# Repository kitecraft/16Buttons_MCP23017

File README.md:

# 16Buttons_MCP23017
A 16 button board using a MCP23017 IC

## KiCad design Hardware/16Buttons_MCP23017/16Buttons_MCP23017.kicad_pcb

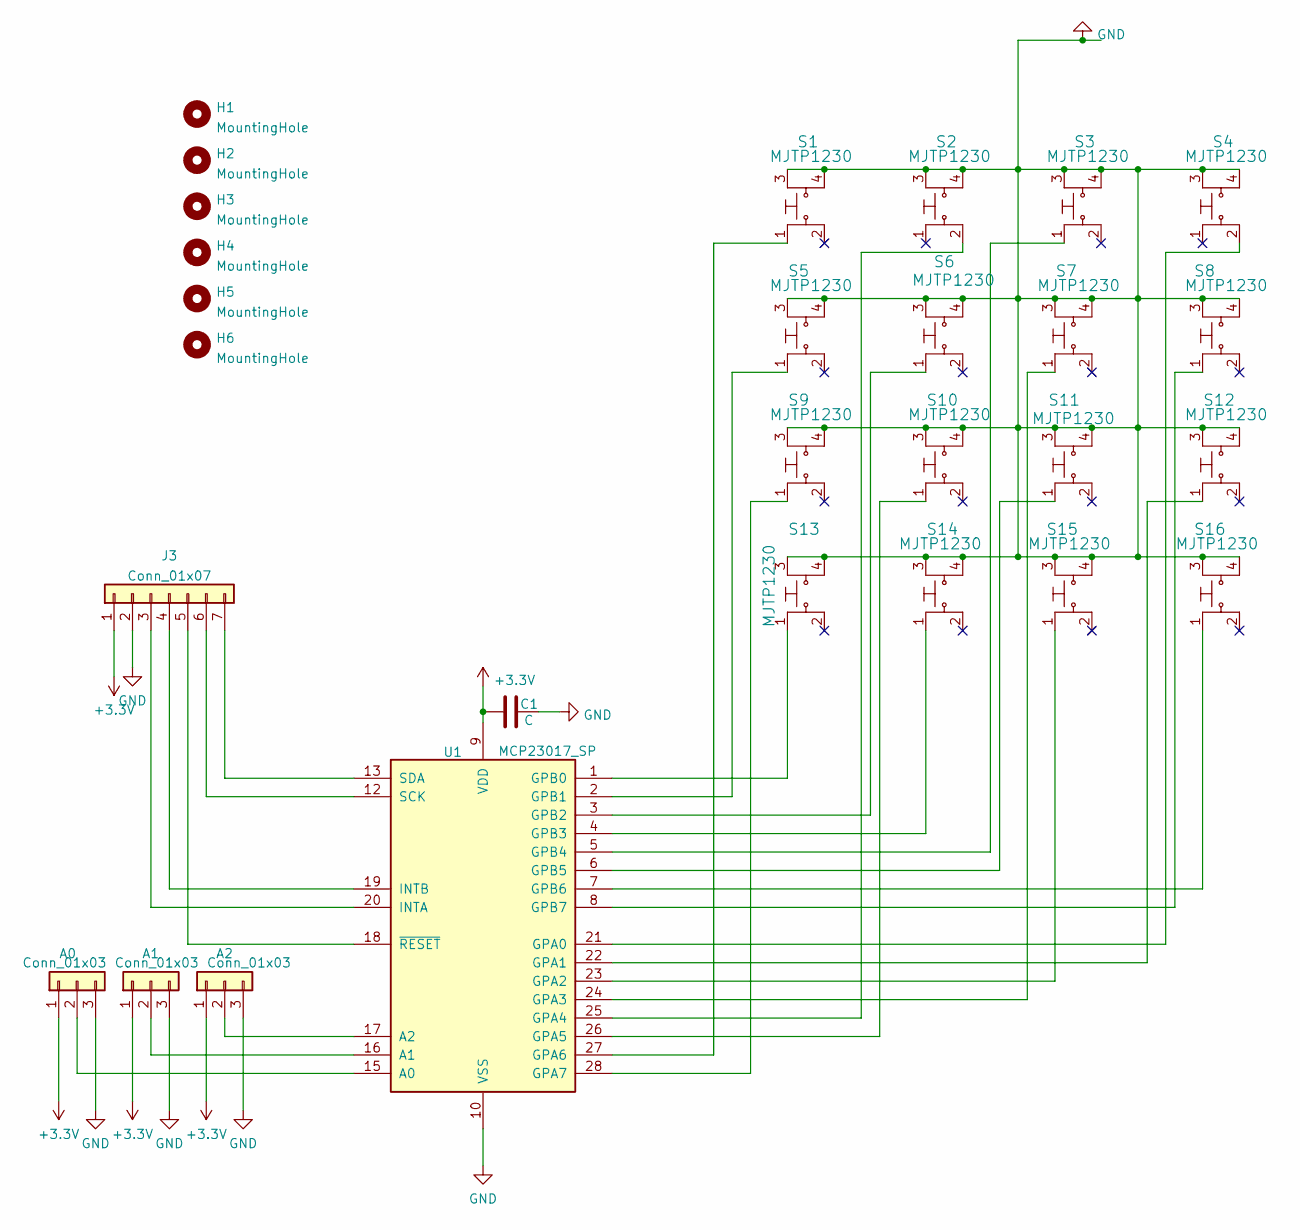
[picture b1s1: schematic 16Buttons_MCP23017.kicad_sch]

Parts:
A0, A1, A2: Conn_01x03; PinHeader_1x03_P2.54mm_Vertical
C1: C; C_Disc_D5.0mm_W2.5mm_P5.00mm
H1, H2, H3, H4, H5, H6: MountingHole; MountingHole_2.2mm_M2
J3: Conn_01x07; PinHeader_1x07_P2.54mm_Vertical
S1, S2, S3, S4, S5, S6, S7, S8, S9, S10, S11, S12, S13, S14, S15, S16: MJTP1230; SW_PUSH_6mm_H4.3mm; MPN MJTP1230; Digi-Key_PN 679-2428-ND
U1: MCP23017_SP; DIP-28_W7.62mm_WithSocket

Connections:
+3V3: A0.1, A1.1, A2.1, C1.1, J3.1, U1.9 (VDD)
GND: A0.3, A1.3, A2.3, C1.2, J3.2, S1.3, S1.4, S2.3, S2.4, S3.3, S3.4, S4.3, S4.4, S5.3, S5.4, S6.3, S6.4, S7.3, S7.4, S8.3, S8.4, S9.3, S9.4, S10.3, S10.4, S11.3, S11.4, S12.3, S12.4, S13.3, S13.4, S14.3, S14.4, S15.3, S15.4, S16.3, S16.4, U1.10 (VSS)
unnamed: A0.2, U1.15 (A0)
unnamed: A1.2, U1.16 (A1)
unnamed: A2.2, U1.17 (A2)
unnamed: J3.3, U1.20 (INTA)
unnamed: J3.4, U1.19 (INTB)
unnamed: J3.5, U1.18 (~RESET)
unnamed: J3.6, U1.12 (SCK)
unnamed: J3.7, U1.13 (SDA)
unnamed: S1.1, U1.27 (GPA6)
unnamed: S2.2, U1.25 (GPA4)
unnamed: S3.1, U1.5 (GPB4)
unnamed: S4.2, U1.21 (GPA0)
unnamed: S5.1, U1.2 (GPB1)
unnamed: S6.1, U1.3 (GPB2)
unnamed: S7.1, U1.24 (GPA3)
unnamed: S8.1, U1.8 (GPB7)
unnamed: S9.1, U1.28 (GPA7)
unnamed: S10.1, U1.26 (GPA5)
unnamed: S11.1, U1.6 (GPB5)
unnamed: S12.1, U1.22 (GPA1)
unnamed: S13.1, U1.1 (GPB0)
unnamed: S14.1, U1.4 (GPB3)
unnamed: S15.1, U1.23 (GPA2)
unnamed: S16.1, U1.7 (GPB6)

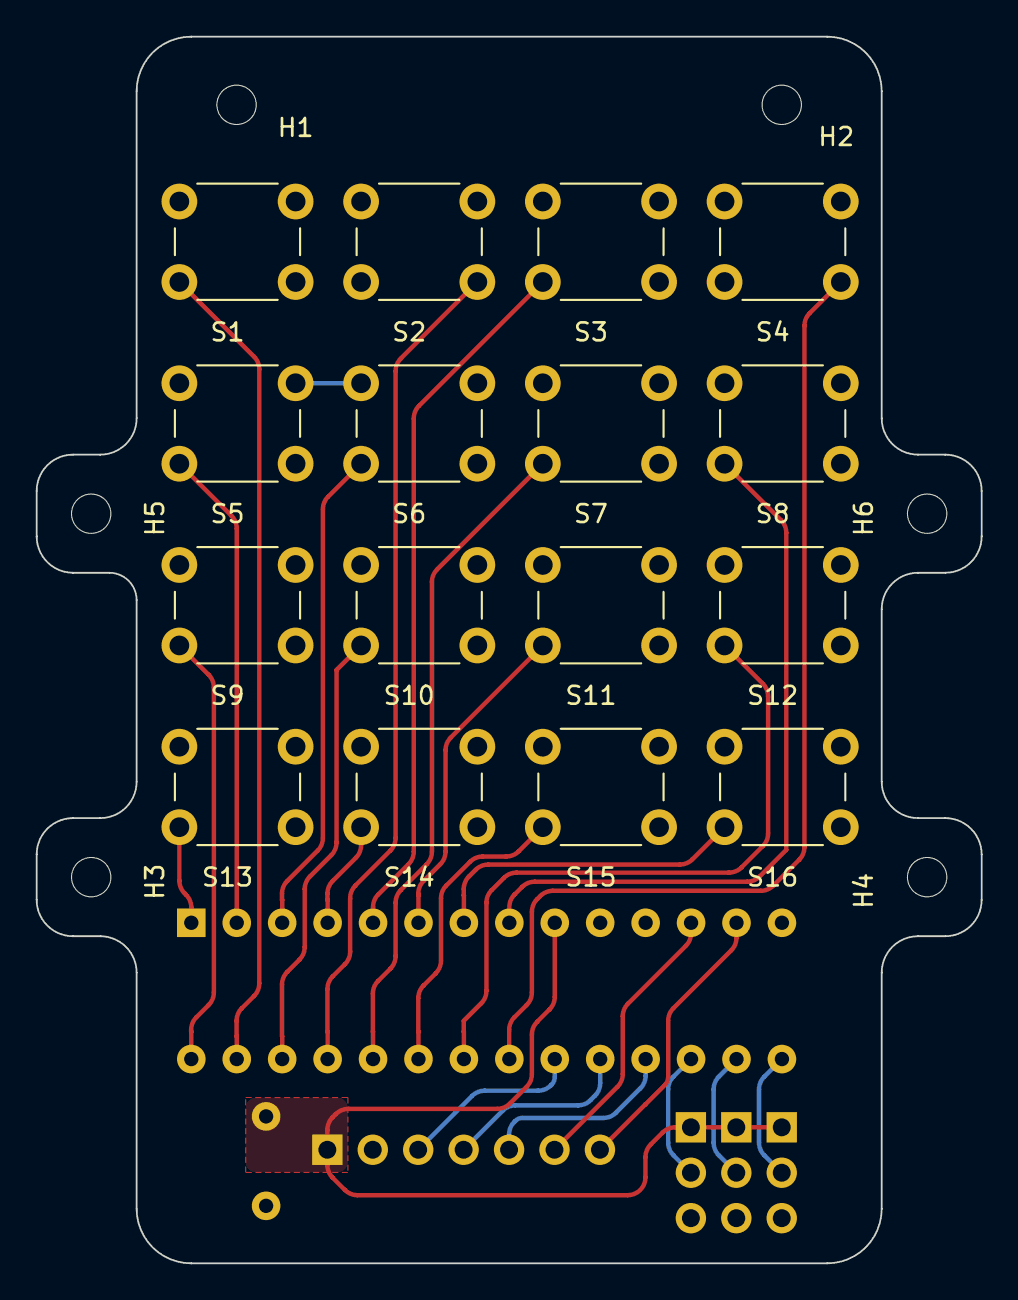
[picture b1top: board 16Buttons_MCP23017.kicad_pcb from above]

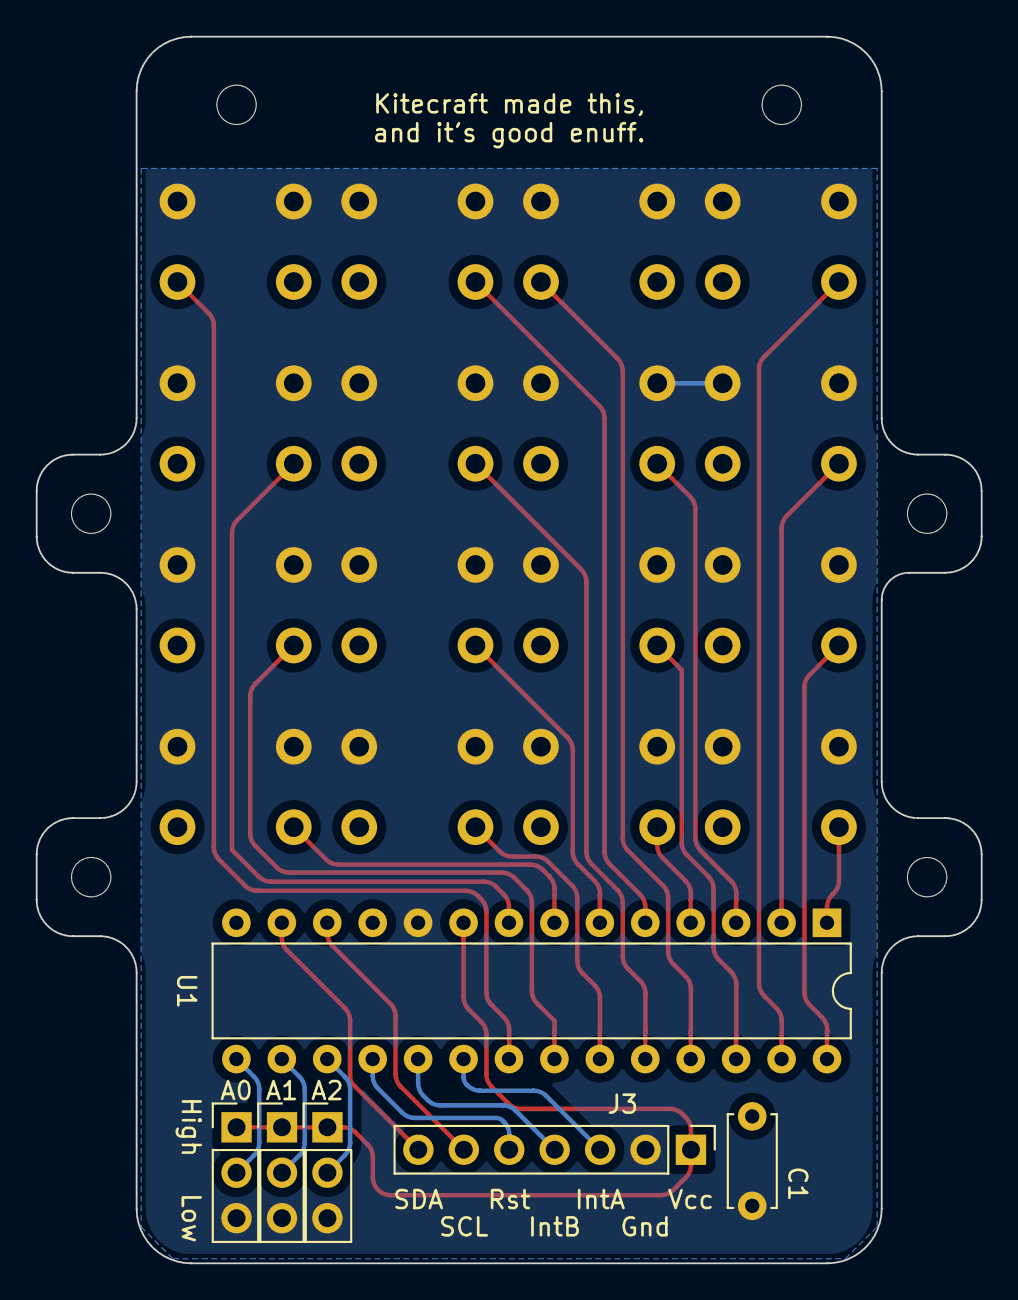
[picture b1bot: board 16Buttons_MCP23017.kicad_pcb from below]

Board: 2 copper layers, 52.8 x 68.6 mm, 28 parts (6 on the bottom side), 26 nets.

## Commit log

2022-02-08 16 button PCB with on-board MCP23017
2022-02-11 Updates.
2022-06-18 Adding Library
2022-09-15 Everything seems to be built and working. PCB's and library both.
2022-09-15 Updated images of PCB
